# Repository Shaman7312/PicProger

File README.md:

# PicProger
A programmer for PIC16 chips.
Only works now with PIC16F886 and a computer SW is crap (only works now if com is COM1).

# Commands for programmer
85  - Enable programming mode. 

170 - Disable programming mode.

18  - Receive command for PIC and store it.

68  - Receive command for PIC and execute immediately.

16  - Reveive 2 Bytes of data and store them.

53  - Execute stored command and send stored data sequentially.

93  - Execute stored command, read 2 Bytes of data from PIC and send them to a computer immediately.

140 - Send stored data to a PIC.

75  - Enable 5V power for PIC.

34  - Disable 5V power for PIC.

# Commands for Pic chip
[Programming specification](http://ww1.microchip.com/downloads/en/DeviceDoc/41287D.pdf)

xxxx0000 + 0,(data 14),0        - Load configuration

xxxx0010 + 0,(data 14),0        - Load data for program memory

xxxx0011 + 0,(data 8), 0000000  - Load data for data memory

xxxx0100 + 0,(data 14),0        - Read data from program memory

xxxx0101 + 0,(data 8), 0000000  - Read data from data memory

xxxx0110                        - Increment address

xxx01000                        - Begin programming (Internal Clock)

xxx11000                        - Begin programming (External Clock)

xxx01010                        - End programming

xxxx1001                        - Bulk erase program memory

xxxx1011                        - Bulk erase data memory

xxx10001                        - Row erase program memory

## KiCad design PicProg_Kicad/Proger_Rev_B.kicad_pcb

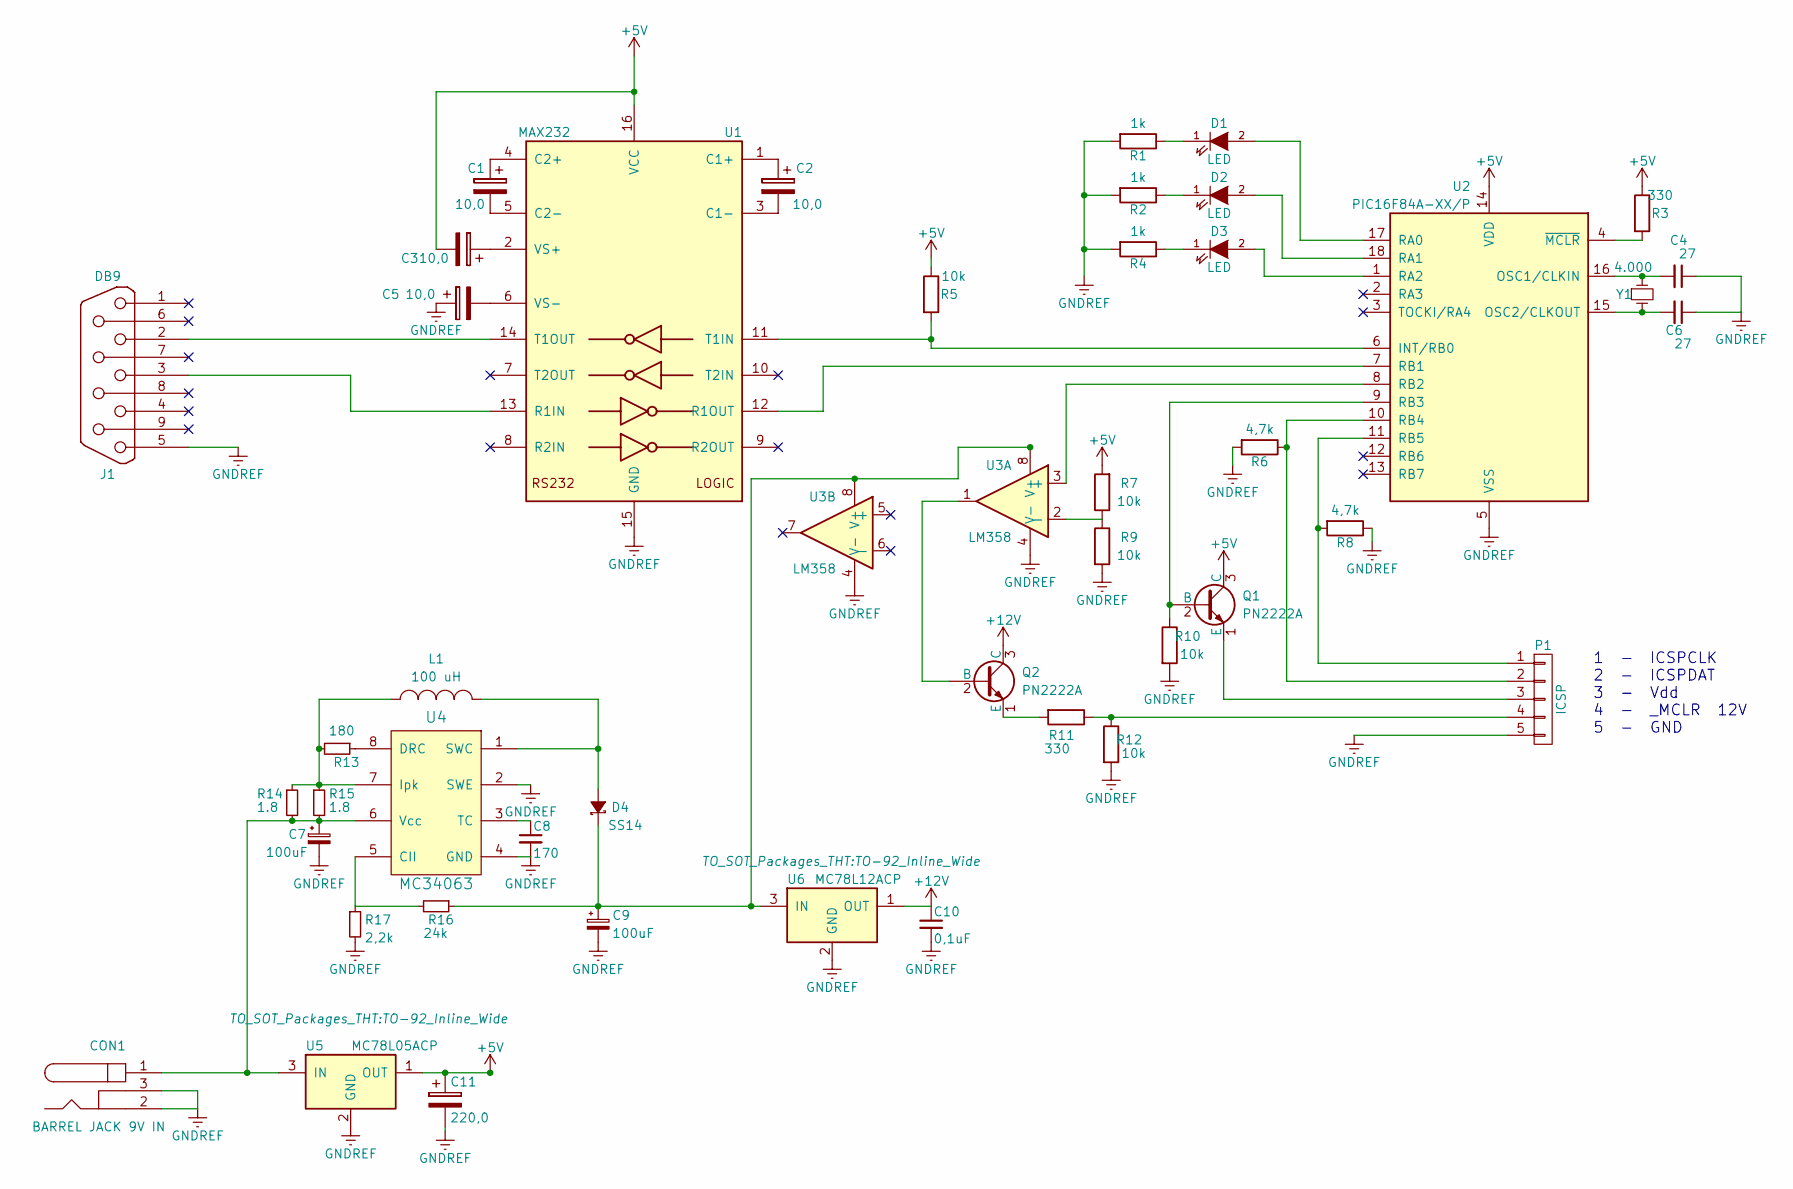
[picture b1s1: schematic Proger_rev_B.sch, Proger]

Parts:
C1, C2, C3, C5: 10,0; C_Radial_D5_L6_P2.5
C4, C6: 27; C_Disc_D7.5_P5
C7, C9: 100uF; C_Radial_D6.3_L11.2_P2.5
C8: 170; C_Disc_D7.5_P5
C10: 0,1uF; C_Rect_L7_W2.5_P5
C11: 220,0; C_Radial_D7.5_L11.2_P2.5
CON1: BARREL JACK 9V IN; BARREL_JACK
D1, D2, D3: LED; LED-5MM
D4: SS14; TantalC_SizeU_EIA-6032
J1: DB9; DB9FC
L1: 100 uH; Choke_Toroid_horizontal_Diameter12-5mm_Amidon-T44
P1: ICSP; Pin_Header_Straight_1x05
Q1, Q2: PN2222A; TO-92_Inline_Wide
R1, R2, R4: 1k; Resistor_Horizontal_RM7mm
R3, R11: 330; Resistor_Horizontal_RM7mm
R5, R7, R9, R10, R12: 10k; Resistor_Horizontal_RM7mm
R6, R8: 4,7k; Resistor_Horizontal_RM7mm
R13: 180; Resistor_Horizontal_RM7mm
R14, R15: 1.8; Resistor_Horizontal_RM7mm
R16: 24k; Resistor_Horizontal_RM7mm
R17: 2,2k; Resistor_Horizontal_RM7mm
U1: MAX232; DIP-16_W7.62mm
U2: PIC16F84A-XX/P; DIP-18_W7.62mm
U3: LM358; DIP-8_W7.62mm
U4: MC34063; SOIC-8_3.9x4.9mm_Pitch1.27mm
U5: MC78L05ACP; TO-92_Inline_Wide
U6: MC78L12ACP; TO-92_Inline_Wide
Y1: 4.000; Crystal_HC49-U_Vertical

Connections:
+5V: C3.2, C11.1, Q1.3 (C), R3.1, R5.1, R7.2, U1.16 (VCC), U2.14 (VDD), U5.1 (OUT)
+12V: C10.1, Q2.3 (C), U6.1 (OUT)
GNDREF: C4.1, C5.1, C6.1, C7.2, C8.2, C9.2, C10.2, C11.2, CON1.2, CON1.3, J1.5, P1.5, R1.2, R2.2, R4.2, R6.2, R8.1, R9.2, R10.2, R12.2, R17.2, U1.15 (GND), U2.5 (VSS), U3.4 (V-), U4.2 (SWE), U4.4 (GND), U5.2 (GND), U6.2 (GND)
unnamed: C1.1, U1.4 (C2+)
unnamed: C1.2, U1.5 (C2-)
unnamed: C2.1, U1.1 (C1+)
unnamed: C2.2, U1.3 (C1-)
unnamed: C3.1, U1.2 (VS+)
unnamed: C4.2, U2.16 (OSC1/CLKIN), Y1.1
unnamed: C5.2, U1.6 (VS-)
unnamed: C6.2, U2.15 (OSC2/CLKOUT), Y1.2
unnamed: C7.1, CON1.1, R14.2, R15.2, U4.6 (Vcc), U5.3 (IN)
unnamed: C8.1, U4.3 (TC)
unnamed: C9.1, D4.1 (K), R16.1, U3.8 (V+), U6.3 (IN)
unnamed: D1.1 (K), R1.1
unnamed: D1.2 (A), U2.17 (RA0)
unnamed: D2.1 (K), R2.1
unnamed: D2.2 (A), U2.18 (RA1)
unnamed: D3.1 (K), R4.1
unnamed: D3.2 (A), U2.1 (RA2)
unnamed: D4.2 (A), L1.2, U4.1 (SWC)
unnamed: J1.2, U1.14 (T1OUT)
unnamed: J1.3, U1.13 (R1IN)
unnamed: L1.1, R13.2, R14.1, R15.1, U4.7 (Ipk)
unnamed: P1.1, R8.2, U2.11 (RB5)
unnamed: P1.2, R6.1, U2.10 (RB4)
unnamed: P1.3, Q1.1 (E)
unnamed: P1.4, R11.1, R12.1
unnamed: Q1.2 (B), R10.1, U2.9 (RB3)
unnamed: Q2.1 (E), R11.2
unnamed: Q2.2 (B), U3.1
unnamed: R3.2, U2.4 (~MCLR~)
unnamed: R5.2, U1.11 (T1IN), U2.6 (INT/RB0)
unnamed: R7.1, R9.1, U3.2 (-)
unnamed: R13.1, U4.8 (DRC)
unnamed: R16.2, R17.1, U4.5 (CII)
unnamed: U1.12 (R1OUT), U2.7 (RB1)
unnamed: U2.8 (RB2), U3.3 (+)

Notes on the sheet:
1 - ICSPCLK 2 - ICSPDAT 3 - Vdd 4 - _MCLR 12V 5 - GND

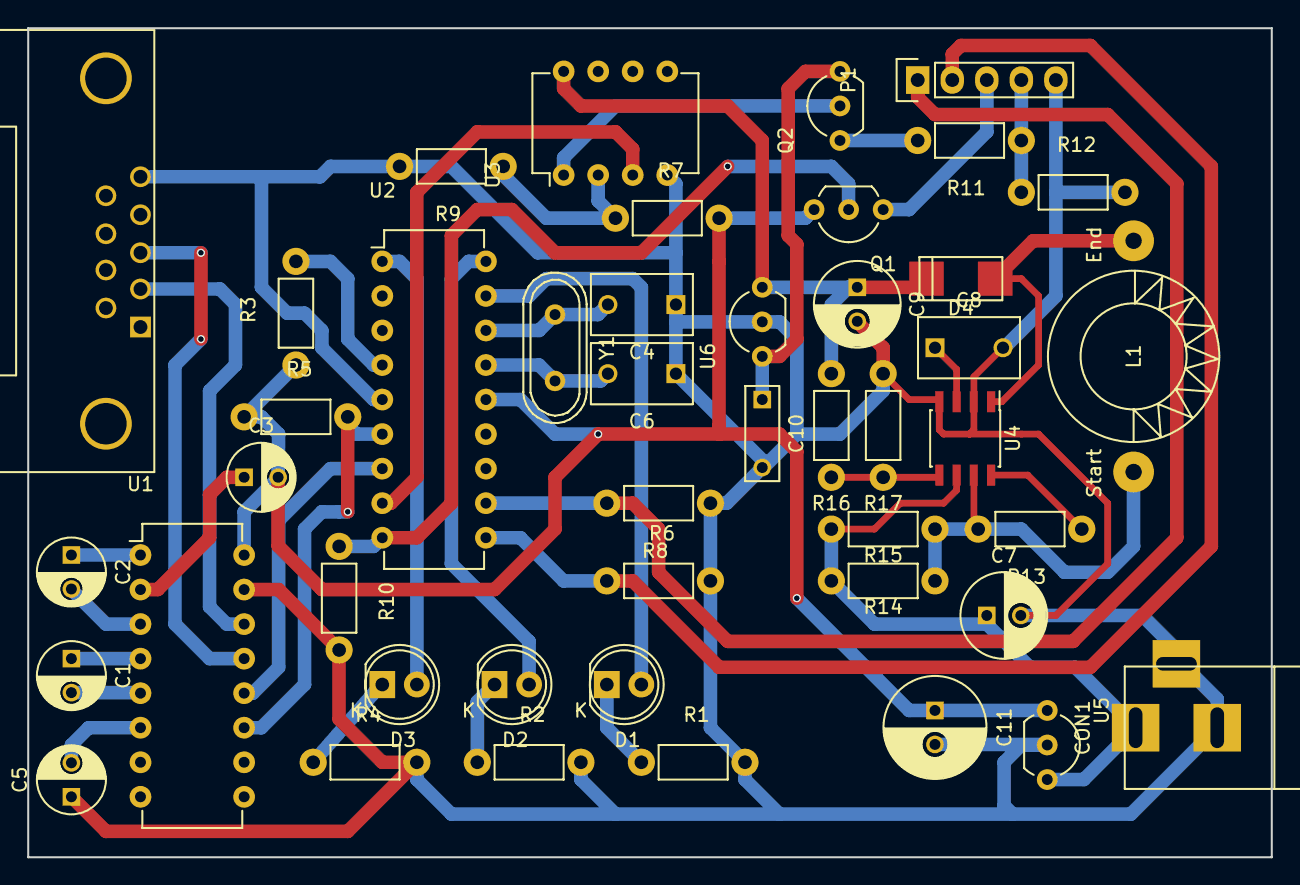
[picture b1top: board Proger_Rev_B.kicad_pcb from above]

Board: 2 copper layers, 91.4 x 61.0 mm, 45 parts (0 on the bottom side), 38 nets.

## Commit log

2017-09-11 Подгрузился из мастера.
